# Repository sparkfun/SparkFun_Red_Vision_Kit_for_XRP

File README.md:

[*SparkFun Red Vision Kit for XRP (KIT-28667)*](https://www.sparkfun.com/sparkfun-pico-vision-kit-for-xrp.html)

The SparkFun Red Vision Kit for XRP comes with the Red Vision Touch Display for Pico and Red Vision Camera Board - HM01B0 (Color) to add add machine vision capabilities to the Experiential Robotics Platform (XRP) Kit. This kit comes with everything you need to quickly and easily add a camera and touchscreen display to your XRP Robot with no soldering required. These boards let you add live image processing as well as advanced features including object and contour detection among others to the Experiential Robotics Platform (XRP) Kit using the SparkFun MicroPython Red Vision Code package, a MicroPython port of the popular OpenCV image processing library.

Repository Contents
-------------------

* **/Hardware** - KiCad design files (.brd, .sch)
* **/docs** - GitHub Pages documentation files

Documentation
--------------
* **[SparkFun Red Vision MicroPython Package](https://github.com/sparkfun/red_vision/tree/main)** - MicroPython package for the SparkFun Red Vision Kit for XRP.
* **[SparkFun MicroPython OpenCV](https://github.com/sparkfun/micropython-opencv)** - MicroPython port of OpenCV code library.
* **[SparkFun MicroPython Firmware Releases](https://github.com/sparkfun/micropython/releases)** - SparkFun MicroPython firmware releases.
* **[SparkFun Red Vision Kit for XRP Hookup Guide](https://docs.sparkfun.com/SparkFun_Red_Vision_Kit_for_XRP/introduction)** - Basic hookup guide for the SparkFun Red Vision Kit for XRP.

Product Versions
----------------
* [KIT-28667](https://www.sparkfun.com/sparkfun-pico-vision-kit-for-xrp.html) - Initial release of the SparkFun Red Vision Kit for XRP
* [LCD-29467](https://www.sparkfun.com/sparkfun-red-vision-touch-display-for-pico.html) - SparkFun Red Vision Touch Display for Pico (Standalone board)
* [SEN-29468](https://www.sparkfun.com/sparkfun-red-vision-camera-board-hm01b0-color.html) - SparkFun Red Vision Camera Board - HM01B0 (Color) (Standalone board)

License Information
-------------------

This product is _**open source**_! 

Please review the LICENSE.md file for license information. 

If you have any questions or concerns on licensing, please contact technical support on our [SparkFun forums](https://forum.sparkfun.com/viewforum.php?f=152).

Distributed as-is; no warranty is given.

- Your friends at SparkFun.

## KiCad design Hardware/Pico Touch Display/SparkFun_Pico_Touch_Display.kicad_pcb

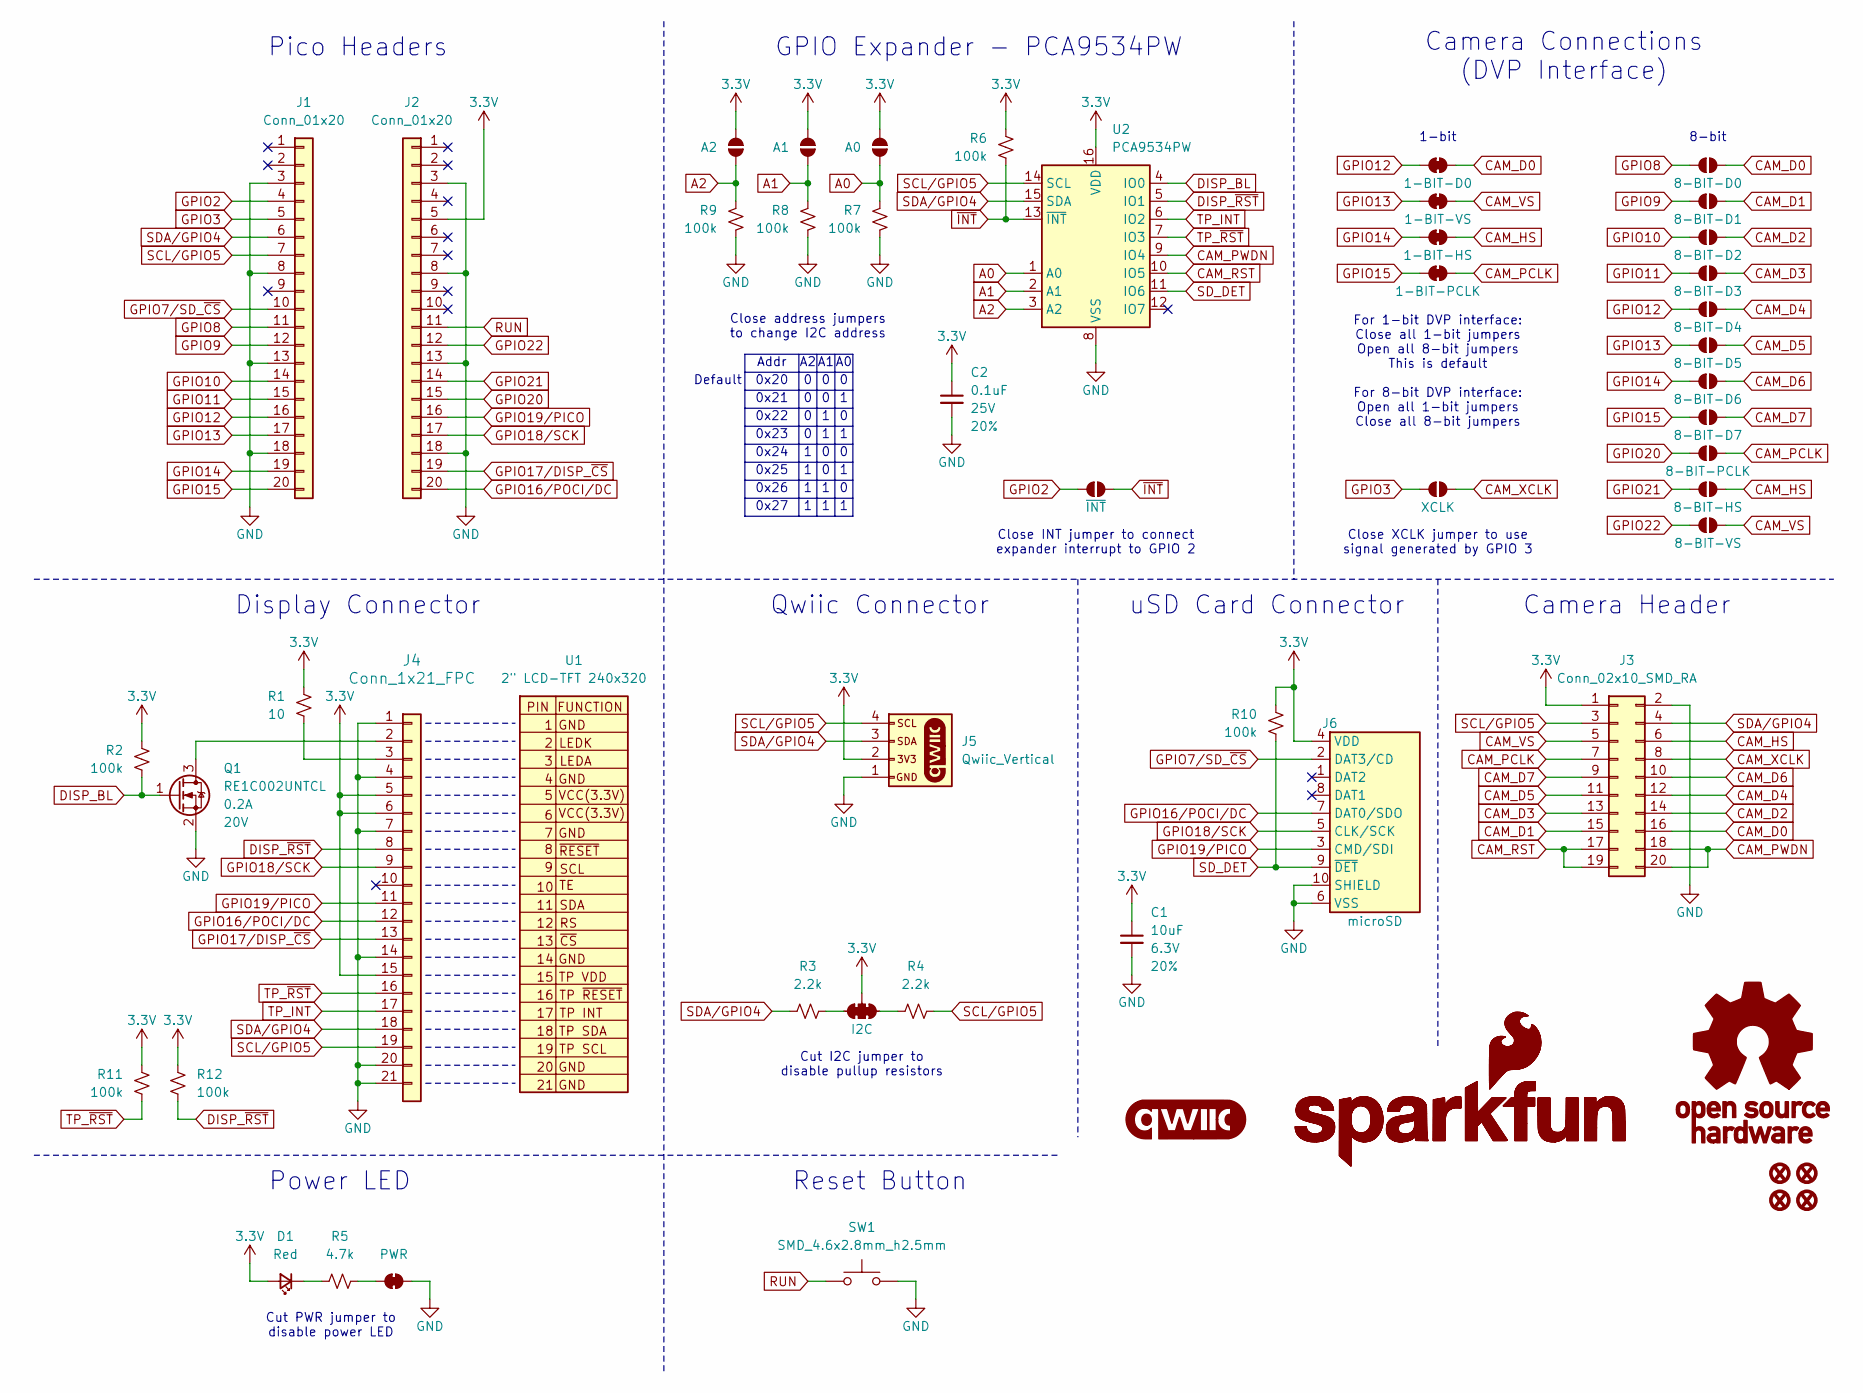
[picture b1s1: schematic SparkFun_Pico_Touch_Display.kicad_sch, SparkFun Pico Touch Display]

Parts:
C1: 10uF; C_0603_1608Metric; Voltage 6.3V; Tolerance 20%
C2: 0.1uF; C_0603_1608Metric; Voltage 25V; Tolerance 20%
D1: Red; LED_0603_1608Metric_Red
FID1, FID2, FID3, FID4: Fiducial_0.5mm; Fiducial_0.5mm_Mask1mm
G1: SparkFun_Logo; SparkFun_Logo_8mm
G2: SparkFun_Logo
G3: OSHW_Logo; Creative_Commons_License
G4: qwiic_Logo
J1, J2: Conn_01x20; 1x20_SMD_Pin1RightUp
J3: Conn_02x10_SMD_RA; 2x10_SMD_RA
J4: Conn_1x21_FPC; CONN21_FH35C-21S_HIR
J5: Qwiic_Vertical; JST_SMD_1.0mm-4_Vertical_Black
J6: microSD; microSD_External_Pin
JP1: I2C; Jumper_3_NC-2_Trace
JP2: 8-BIT-D0; Jumper_2_NO
JP3: 8-BIT-VS; Jumper_2_NO
JP4: 8-BIT-HS; Jumper_2_NO
JP5: 8-BIT-PCLK; Jumper_2_NO
JP6: 8-BIT-D3; Jumper_2_NO
JP7: 8-BIT-D2; Jumper_2_NO
JP8: 8-BIT-D1; Jumper_2_NO
JP9: 8-BIT-D4; Jumper_2_NO
JP10: 8-BIT-D5; Jumper_2_NO
JP11: 8-BIT-D6; Jumper_2_NO
JP12: 8-BIT-D7; Jumper_2_NO
JP13: XCLK; Jumper_2_NO
JP14: A0; Jumper_2_NO
JP15: A1; Jumper_2_NO
JP16: A2; Jumper_2_NO
JP17: 1-BIT-PCLK; Jumper_2_NC_Trace
JP18: 1-BIT-HS; Jumper_2_NC_Trace
JP19: 1-BIT-VS; Jumper_2_NC_Trace
JP20: 1-BIT-D0; Jumper_2_NC_Trace
JP21: PWR; Jumper_2_NC_Trace
JP22: ~{INT}; Jumper_2_NO
Q1: RE1C002UNTCL; SC-89 SOT-490
R1: 10; R_0603_1608Metric
R2, R6, R7, R8, R9, R10, R11, R12: 100k; R_0603_1608Metric
R3, R4: 2.2k; R_0603_1608Metric
R5: 4.7k; R_0603_1608Metric
SW1: SMD_4.6x2.8mm_h2.5mm; Push_SMD_4.6x2.8mm_h2.5mm
U1: 2" LCD-TFT 240x320; Waveshare_2_Inch_Outline
U2: PCA9534PW; TSSOP-16_4.4x5mm_P0.65mm

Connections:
3.3V: C1.1, C2.1, D1.2 (A), J2.5, J3.1, J4.5, J4.6, J4.15, J5.2, J6.4 (VDD), JP1.2 (B), JP14.2 (B), JP15.2 (B), JP16.2 (B), R1.2, R2.2, R6.2, R10.2, R11.2, R12.2, U2.16 (VDD)
A0: JP14.1 (A), R7.2, U2.1 (A0)
A1: JP15.1 (A), R8.2, U2.2 (A1)
A2: JP16.1 (A), R9.2, U2.3 (A2)
CAM_D0: J3.16, JP2.2 (B), JP20.1 (A)
CAM_D1: J3.15, JP8.1 (A)
CAM_D2: J3.14, JP7.1 (A)
CAM_D3: J3.13, JP6.1 (A)
CAM_D4: J3.12, JP9.1 (A)
CAM_D5: J3.11, JP10.1 (A)
CAM_D6: J3.10, JP11.1 (A)
CAM_D7: J3.9, JP12.1 (A)
CAM_HS: J3.6, JP4.2 (B), JP18.1 (A)
CAM_PCLK: J3.7, JP5.2 (B), JP17.1 (A)
CAM_PWDN: J3.18, J3.20, U2.9 (IO4)
CAM_RST: J3.17, J3.19, U2.10 (IO5)
CAM_VS: J3.5, JP3.2 (B), JP19.1 (A)
CAM_XCLK: J3.8, JP13.1 (A)
DISP_BL: Q1.1 (G), R2.1, U2.4 (IO0)
DISP_~RST: J4.8, R12.1, U2.5 (IO1)
GND: C1.2, C2.2, J1.3, J1.8, J1.13, J1.18, J2.3, J2.8, J2.13, J2.18, J3.2, J4.1, J4.4, J4.7, J4.14, J4.20, J4.21, J5.1, J6.6 (VSS), J6.10 (SHIELD), JP21.2 (B), Q1.2 (S), R7.1, R8.1, R9.1, SW1.2, U2.8 (VSS)
GPIO2: J1.4, JP22.2 (B)
GPIO3: J1.5, JP13.2 (B)
GPIO7/SD_~CS: J1.10, J6.2 (DAT3/CD)
GPIO8: J1.11, JP2.1 (A)
GPIO9: J1.12, JP8.2 (B)
GPIO10: J1.14, JP7.2 (B)
GPIO11: J1.15, JP6.2 (B)
GPIO12: J1.16, JP9.2 (B), JP20.2 (B)
GPIO13: J1.17, JP10.2 (B), JP19.2 (B)
GPIO14: J1.19, JP11.2 (B), JP18.2 (B)
GPIO15: J1.20, JP12.2 (B), JP17.2 (B)
GPIO16/POCI/DC: J2.20, J4.12, J6.7 (DAT0/SDO)
GPIO17/DISP_~CS: J2.19, J4.13
GPIO18/SCK: J2.17, J4.9, J6.5 (CLK/SCK)
GPIO19/PICO: J2.16, J4.11, J6.3 (CMD/SDI)
GPIO20: J2.15, JP5.1 (A)
GPIO21: J2.14, JP4.1 (A)
GPIO22: J2.12, JP3.1 (A)
unnamed: D1.1 (K), R5.2
unnamed: J4.2, Q1.3 (D)
unnamed: J4.3, R1.1
unnamed: JP1.1 (A), R4.1
unnamed: JP1.3 (C), R3.2
unnamed: JP21.1 (A), R5.1
RUN: J2.11, SW1.1
SCL/GPIO5: J1.7, J3.3, J4.19, J5.4, R4.2, U2.14 (SCL)
SDA/GPIO4: J1.6, J3.4, J4.18, J5.3, R3.1, U2.15 (SDA)
SD_DET: J6.9 (~DET), R10.1, U2.11 (IO6)
TP_INT: J4.17, U2.6 (IO2)
TP_~RST: J4.16, R11.1, U2.7 (IO3)
~INT: JP22.1 (A), R6.1, U2.13 (~INT)

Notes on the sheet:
1-bit
0x20
8-bit
Cut PWR jumper to disable power LED
0x22
0x27
0x24
GPIO Expander - PCA9534PW
Camera Connections (DVP Interface)
Close address jumpers to change I2C address
Default
Addr
Qwiic Connector
Cut I2C jumper to disable pullup resistors
Pico Headers
Camera Header
0x26
For 1-bit DVP interface: Close all 1-bit jumpers Open all 8-bit jumpers This is default For 8-bit DVP interface: Open all 1-bit jumpers Close all 8-bit jumpers
0x23
Display Connector
Close XCLK jumper to use signal generated by GPIO 3
0x21
uSD Card Connector
0x25
Power LED
Reset Button
Close INT jumper to connect expander interrupt to GPIO 2

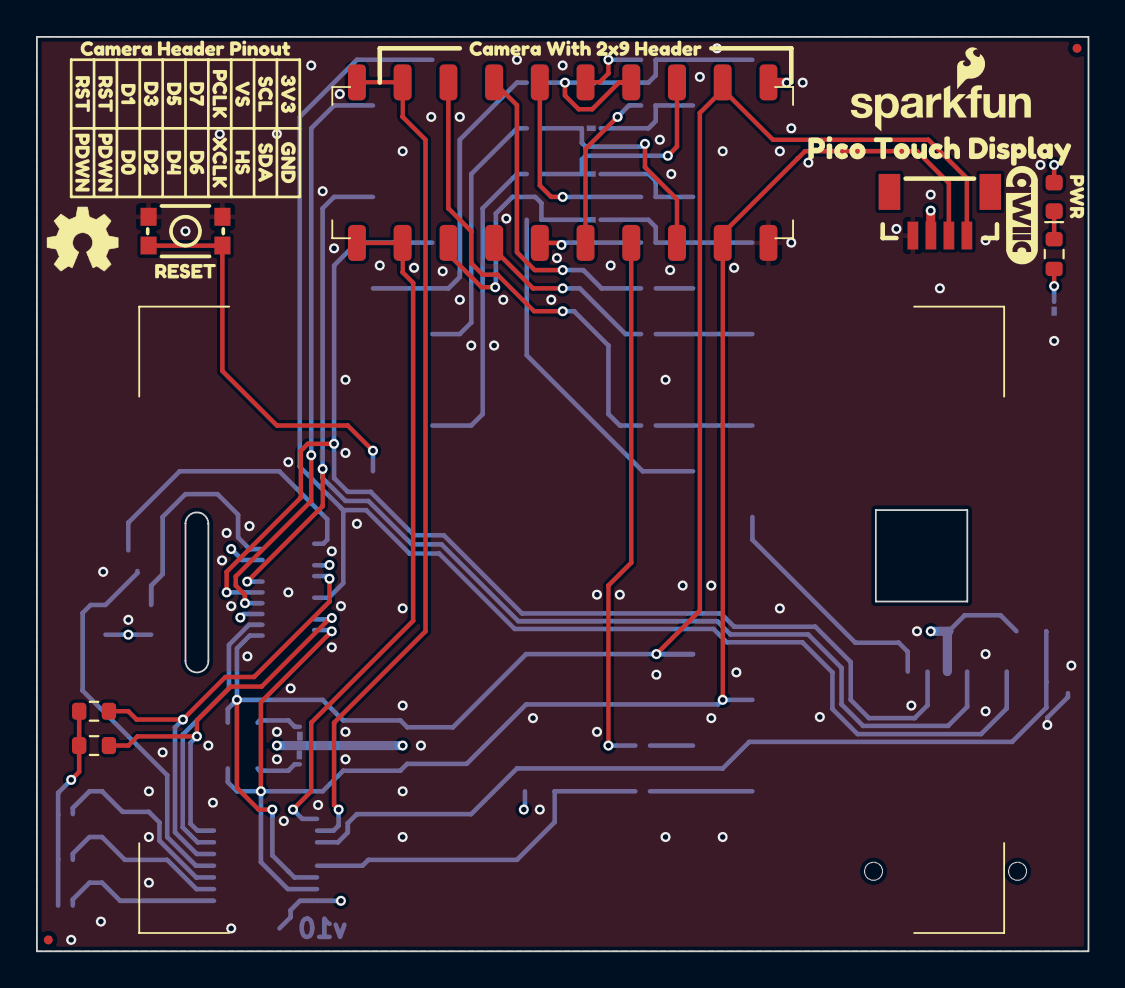
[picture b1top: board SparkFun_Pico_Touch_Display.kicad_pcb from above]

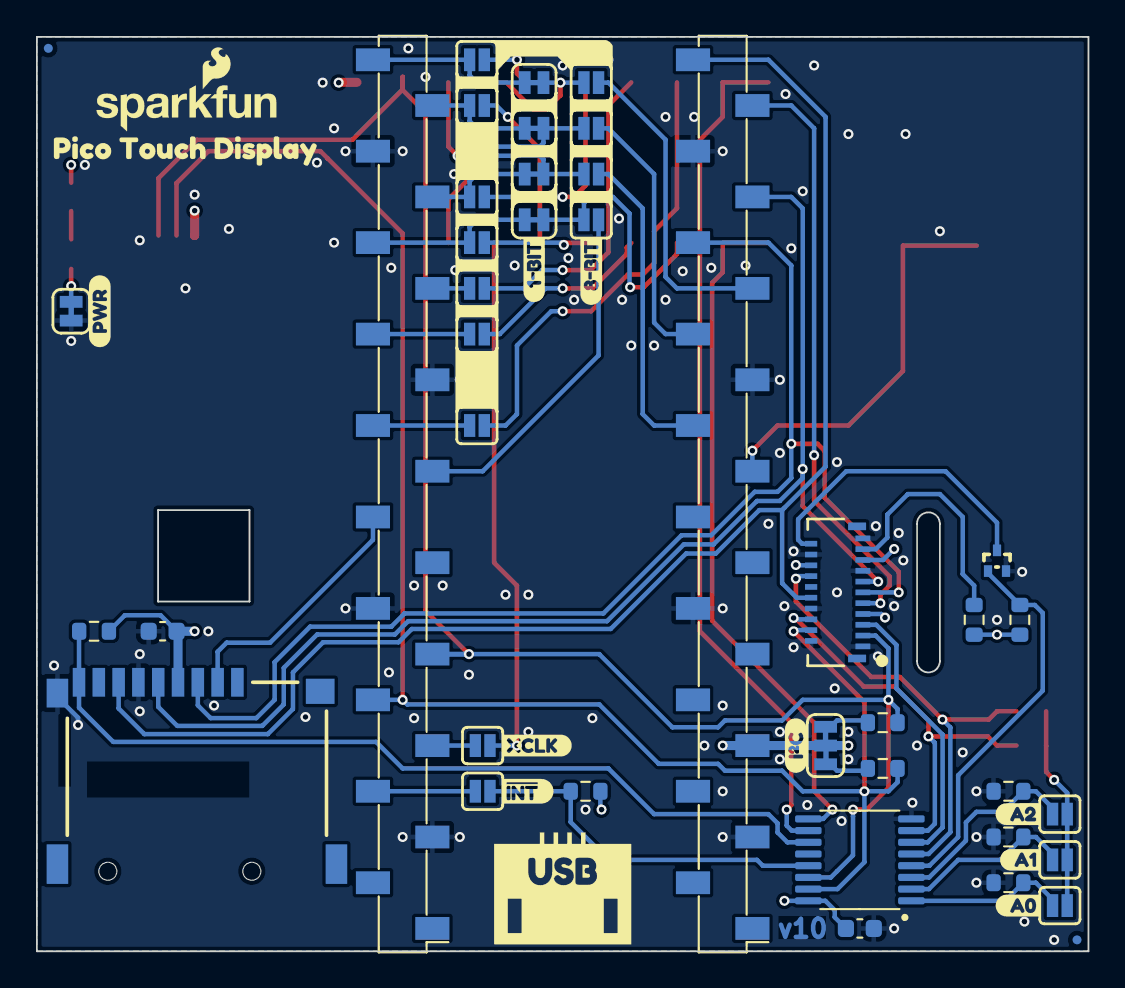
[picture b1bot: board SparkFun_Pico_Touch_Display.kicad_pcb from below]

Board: 4 copper layers, 58.4 x 50.8 mm, 89 parts (52 on the bottom side), 52 nets.

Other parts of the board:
Ref**: Val**; OSHW_Logo_4mm
kibuzzard-67A69C5F, kibuzzard-67A69C5F#2: G***; kibuzzard-67A69C5F
kibuzzard-67A69CD2, kibuzzard-67A69CD2#2: G***; kibuzzard-67A69CD2
kibuzzard-67A69CDC: G***; kibuzzard-67A69CDC
kibuzzard-67A69CE2: G***; kibuzzard-67A69CE2
kibuzzard-67A69CE6: G***; kibuzzard-67A69CE6
kibuzzard-67A69CEA: G***; kibuzzard-67A69CEA
kibuzzard-67A69CFF: G***; kibuzzard-67A69CFF
kibuzzard-67A69D0C: G***; kibuzzard-67A69D0C
kibuzzard-67A69D0F: G***; kibuzzard-67A69D0F
kibuzzard-67A69D1B: G***; kibuzzard-67A69D1B
kibuzzard-67A69D2C: G***; kibuzzard-67A69D2C
kibuzzard-67A69D2F: G***; kibuzzard-67A69D2F
kibuzzard-67A69D05: G***; kibuzzard-67A69D05
kibuzzard-67A69D16: G***; kibuzzard-67A69D16
kibuzzard-67A69D28: G***; kibuzzard-67A69D28
kibuzzard-67A69D32: G***; kibuzzard-67A69D32
kibuzzard-67A69E51: G***; kibuzzard-67A69E51
kibuzzard-67A69E55: G***; kibuzzard-67A69E55
kibuzzard-67ABB7DF: G***; kibuzzard-67ABB7DF
kibuzzard-67B3EC79, kibuzzard-67B3EC79#2: G***; kibuzzard-67B3EC79
kibuzzard-67B3EC92: G***; kibuzzard-67B3EC92
kibuzzard-67B3F617: G***; kibuzzard-67B3F617
kibuzzard-67B3FF40: G***; kibuzzard-67B3FF40
kibuzzard-67B3FF54: G***; kibuzzard-67B3FF54
kibuzzard-67B3FFE0: G***; kibuzzard-67B3FFE0
kibuzzard-67C124A5: G***; kibuzzard-67C124A5
kibuzzard-67C651AF: G***; kibuzzard-67C651AF
kibuzzard-67C1248C: G***; kibuzzard-67C1248C
kibuzzard-67C6452E: G***; kibuzzard-67C6452E
kibuzzard-67C64429: G***; kibuzzard-67C64429
kibuzzard-67C64532: G***; kibuzzard-67C64532
kibuzzard-681E5A39: G***; kibuzzard-681E5A39
kibuzzard-681E525B: G***; kibuzzard-681E525B

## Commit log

2025-07-01 Initial commit
    Updating from repo template. Adding hardware files & docs template files.
2025-08-06 Docs review update
    Major content update from intial docs commit. Adding images & review changes prior to final review & GH pages build.
2025-08-07 Final review updates
    Final review changes and adding GitHub pages build files.
2025-08-07 Deployed d8f918a with MkDocs version: 1.6.1
2025-08-07 Update README.md
    Update README.md from template
2025-08-07 Deployed d6867fa with MkDocs version: 1.6.1
2025-08-12 Adding annotated photos
    Update to hardware overview pages with annotated photos of Camera and Touch Display boards.
2025-08-12 Deployed 7046198 with MkDocs version: 1.6.1
2025-08-12 Adding banner photos
    Adding banner photos to intro & readme
2025-08-12 Deployed 48784fc with MkDocs version: 1.6.1
2026-06-03 Deployed 31d1a20 with MkDocs version: 1.6.1

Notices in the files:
parts and their libraries:
https://creativecommons.org/licenses/by-sa/4.0
Released under the Creative Commons Attribution Share-Alike 4.0 License
